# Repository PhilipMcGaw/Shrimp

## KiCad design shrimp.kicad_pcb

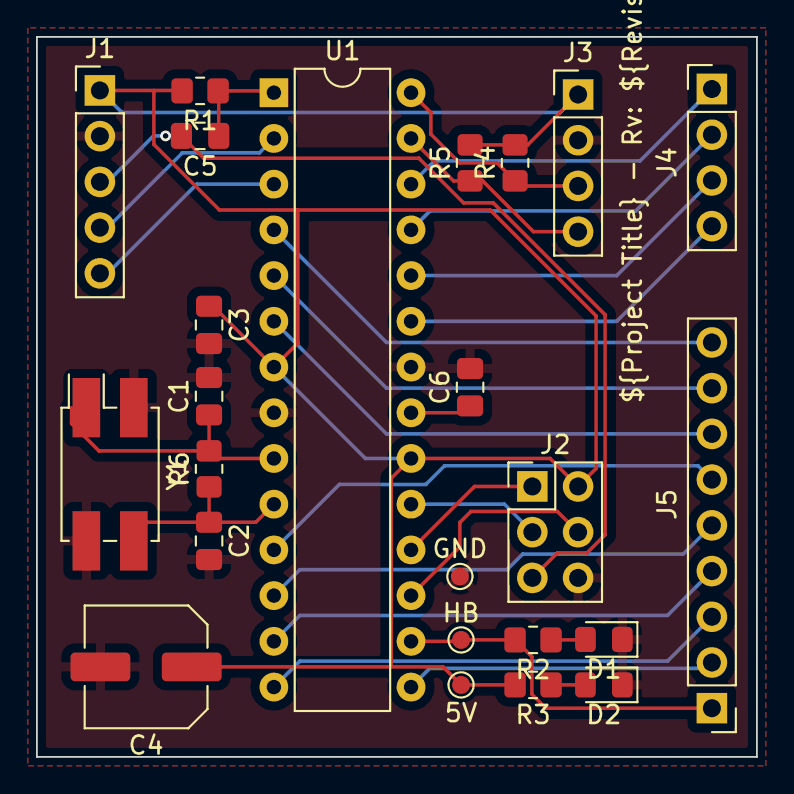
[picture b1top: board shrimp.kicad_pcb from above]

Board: 2 copper layers, 40.0 x 40.0 mm, 24 parts (0 on the bottom side), 29 nets.

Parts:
C1, C2: 22pF; C_0805_2012Metric_Pad1.18x1.45mm_HandSolder
C3, C5, C6: 100nF; C_0805_2012Metric_Pad1.18x1.45mm_HandSolder
C4: 10uF; C_Elec_6.3x5.8
D1: Red; D_0805_2012Metric_Pad1.15x1.40mm_HandSolder
D2: Green; D_0805_2012Metric_Pad1.15x1.40mm_HandSolder
J1: UART; PinHeader_1x05_P2.54mm_Vertical
J2: ICSP; PinHeader_2x03_P2.54mm_Vertical
J3: I2C; PinHeader_1x04_P2.54mm_Vertical
J4: Analouge; PinHeader_1x04_P2.54mm_Vertical
J5: Digital; PinHeader_1x09_P2.54mm_Vertical
R1, R4, R5: 10k; R_0805_2012Metric_Pad1.20x1.40mm_HandSolder
R2, R3: 1k; R_0805_2012Metric_Pad1.20x1.40mm_HandSolder
R6: 1M; R_0805_2012Metric_Pad1.20x1.40mm_HandSolder
TP1: 5V; TestPoint_Pad_D1.0mm
TP2: GND; TestPoint_Pad_D1.0mm
TP3: HB; TestPoint_Pad_D1.0mm
U1: ATmega328P-P; DIP-28_W7.62mm
Y1: 16 MHz; Crystal_SMD_EuroQuartz_MQ-4Pin_7.0x5.0mm_HandSoldering

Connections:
+5V: C3.1, C4.1, J1.1, J2.2, J3.1, R1.2, R3.2, R4.2, R5.2, TP1.1, U1.7 (VCC), U1.20 (AVCC)
/A0: J4.4, U1.23 (PC0)
/A1: J4.3, U1.24 (PC1)
/A2: J4.2, U1.25 (PC2)
/A3: J4.1, U1.26 (PC3)
/D2: J5.9, U1.4 (PD2)
/D3~: J5.8, U1.5 (PD3)
/D4: J5.7, U1.6 (PD4)
/D5~: J5.6, U1.11 (PD5)
/D6~: J5.5, U1.12 (PD6)
/D7: J5.4, U1.13 (PD7)
/D8: J5.3, U1.14 (PB0)
/D9~: J5.2, U1.15 (PB1)
/D10~: J5.1, R2.2, TP3.1, U1.16 (PB2)
/MISO: J2.1, U1.18 (PB4)
/MOSI: J2.4, U1.17 (PB3)
/RX: J1.4, U1.2 (PD0)
/Reset: C5.2, J1.3, J2.5
/SCK: J2.3, U1.19 (PB5)
/SCL: J3.3, R4.1, U1.28 (PC5)
/SDA: J3.4, R5.1, U1.27 (PC4)
/TX: J1.5, U1.3 (PD1)
GND: C1.2, C2.2, C3.2, C4.2, C6.2, D1.1 (K), D2.1 (K), J1.2, J2.6, J3.2, TP2.1, U1.8 (GND), U1.22 (GND), Y1.2, Y1.4
unnamed: D1.2 (A), R2.1
unnamed: D2.2 (A), R3.1
unnamed: C6.1, U1.21 (AREF)
unnamed: C1.1, R6.2, U1.9 (XTAL1/PB6), Y1.1
unnamed: C2.1, R6.1, U1.10 (XTAL2/PB7), Y1.3
unnamed: C5.1, R1.1, U1.1 (~RESET/PC6)

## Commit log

2024-12-12 Added KiCAD common
2024-12-12 updated paths to use the KiCAD Common sub-module
2024-12-12 updated sub-module
2024-12-16 updated sub module
